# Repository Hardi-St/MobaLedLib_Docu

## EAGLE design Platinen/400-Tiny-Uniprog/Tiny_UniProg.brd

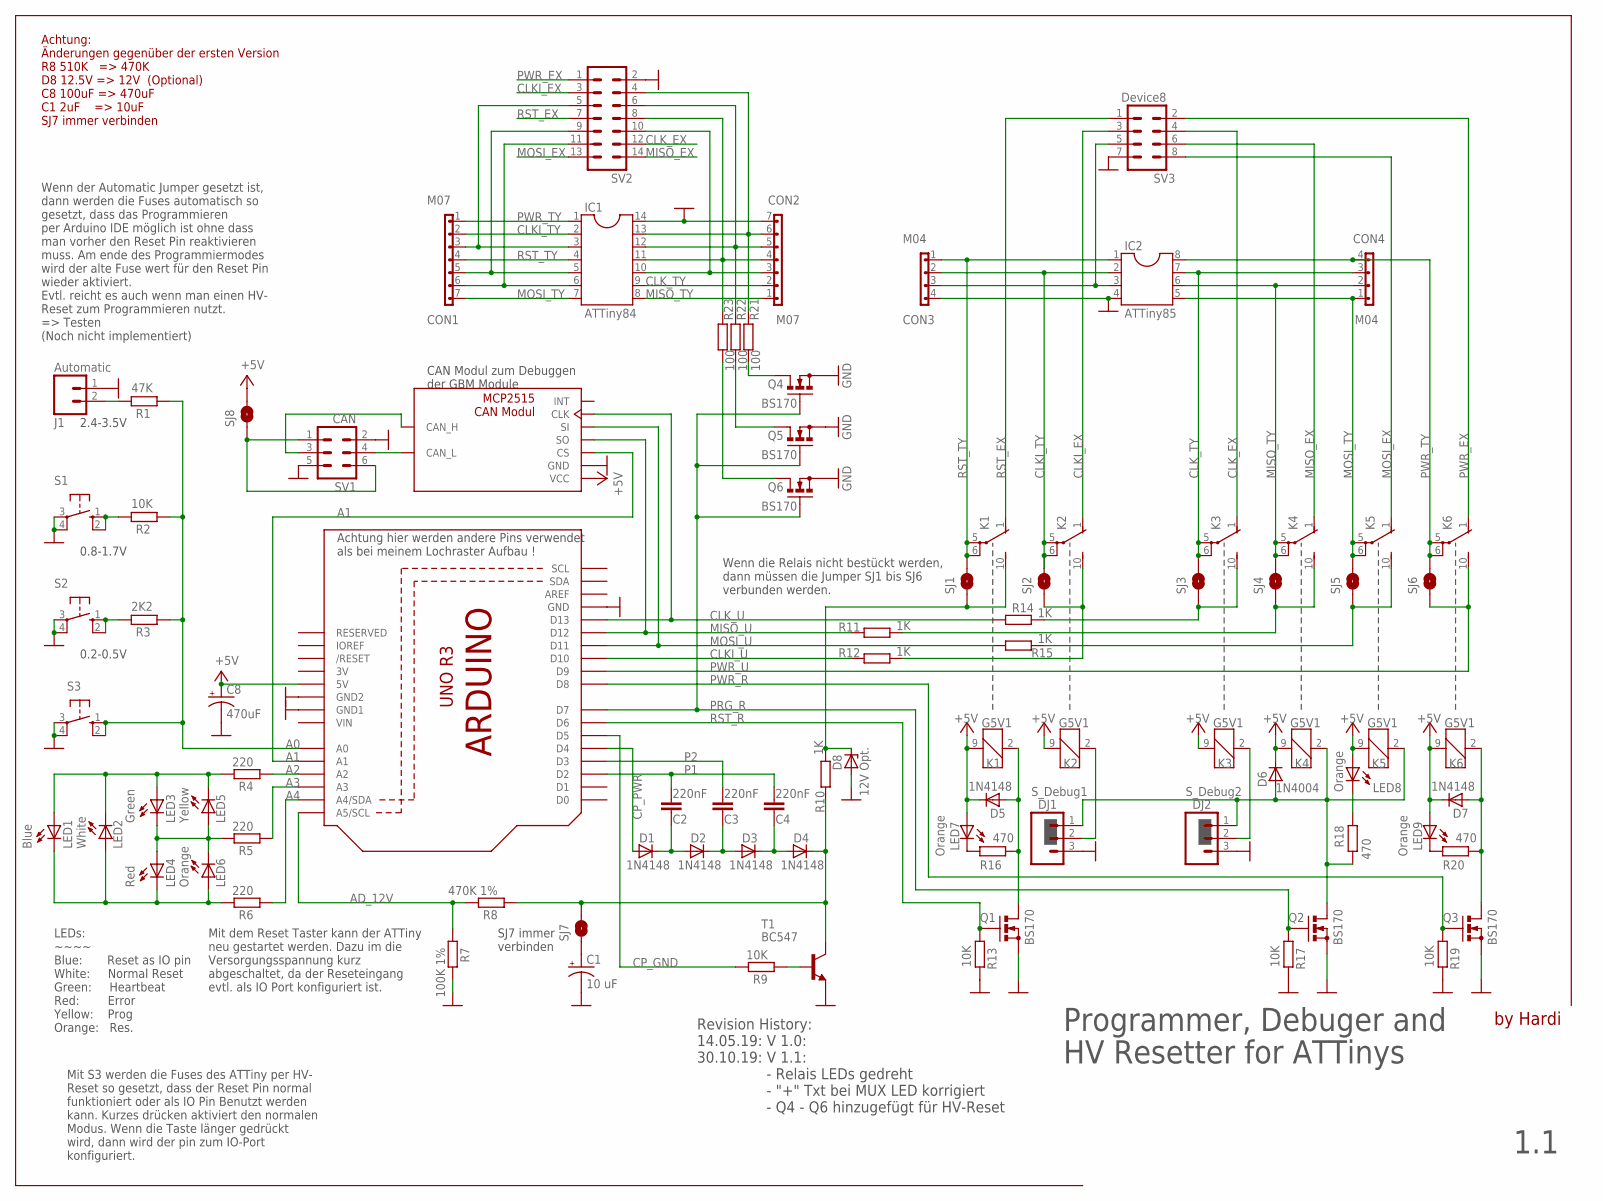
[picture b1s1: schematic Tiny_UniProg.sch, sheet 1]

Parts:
C1: 10 uF; CPOL-RADIAL-10UF-63V
C2, C3, C4: 220nF; C050-024X044
C8: 470uF; SPARKFUN-CAPACITORS_CPOL-RADIAL-100UF-25V
CAN1: MCP2515_CAN_MODUL
CON1, CON2: M07; 1X07
CON3, CON4: M04; 1X04
D1, D2, D3, D4, D5, D7: 1N4148; DO35-2
D6: 1N4004; DO35-2
D8: 12V Opt.; ZDIO-2.5
DJ1: S_Debug1; 1X03
DJ2: S_Debug2; 1X03
IC1: ATTiny84; DIL14
IC2: ATTiny85; DIL08
J1: Automatic; 1X02
K1, K2, K3, K4, K5, K6: G5V1
LED1: Blue; LED3MM
LED2: White; LED3MM
LED3: Green; LED3MM
LED4: Red; LED3MM
LED5: Yellow; LED3MM
LED6, LED7, LED8, LED9: Orange; LED3MM
Q1, Q2, Q3, Q4, Q5, Q6: BS170; SOT54E
R1: 47K; 0204/7
R2: 10K; 0204/7
R3: 2K2; 0204/2V
R4, R5, R6: 220; 0204/2V
R7: 100K 1%; 0204/2V
R8: 470K 1%; 0204/7
R9, R13, R17, R19: 10K; 0204/2V
R10, R11, R12, R14, R15: 1K; 0204/2V
R16, R18, R20: 470; 0204/2V
R21, R22, R23: 100; 0204/2V
S1, S2, S3: 10-XX; B3F-10XX
SJ1, SJ2, SJ3, SJ4, SJ5, SJ6, SJ7, SJ8: SOLDERJUMPERNO; SJ_2S-NO
SV1: CAN; ML6
SV2: ML14
SV3: Device8; CON-HARTING-ML_ML08
T1: BC547; TO92
U1: ARDUINOR3-DIMENSION; ARDUINOR3

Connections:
3V: U1.3V
+5V: C8.1 (+), CAN1.1 (VCC), D5.C, D6.C, D7.C, K1.9 (2), K2.9 (2), K3.9 (2), K4.9 (2), K5.9 (2), K6.9 (2), LED7.A, LED8.A, LED9.A, SJ8.2, U1.5V
A0: R1.1, R2.1, R3.1, S3.1 (S), S3.2 (S1), U1.A0
A1: CAN1.3 (CS), U1.A1
A2: R4.1, U1.A2
A3: R5.1, U1.A3
A4: R6.1, U1.A4 (A4/SDA)
AD_12V: R7.1, R8.2, U1.A5 (A5/SCL)
CLKI_EX: K2.1 (O), SV2.3, SV3.3
CLKI_TY: CON1.2, CON3.2, IC1.2, IC2.2, K2.5, K2.6, SJ2.2
CLKI_U: R12.1, U1.D10
CLK_EX: K3.1 (O), SV2.12, SV3.4
CLK_TY: CON2.2, CON4.3, IC1.9, IC2.7, K3.5, K3.6, SJ3.2
CLK_U: CAN1.6 (CLK), R14.1, U1.D13
CP_GND: R9.2, U1.D5
CP_PWR: D1.A, U1.D4
GND: C1.2 (-), C8.2 (-), CAN1.2 (GND), CON2.7, CON3.4, D8.A, DJ1.3, DJ2.3, IC1.14, IC2.4, J1.1, Q1.S, Q2.S, Q3.S, Q4.S, Q5.S, Q6.S, R7.2, R13.2, R17.2, R19.2, S1.3, S1.4 (P1), S2.3, S2.4 (P1), S3.3, S3.4 (P1), SV1.2, SV1.5, SV2.2, SV3.7, T1.1 (E), U1.GND, U1.GND1, U1.GND2
MISO_EX: K4.1 (O), SV2.14, SV3.6
MISO_TY: CON2.1, CON4.2, IC1.8, IC2.6, K4.5, K4.6, SJ4.2
MISO_U: CAN1.4 (SO), R11.1, U1.D12
MOSI_EX: K5.1 (O), SV2.13, SV3.8
MOSI_TY: CON1.7, CON4.1, IC1.7, IC2.5, K5.5, K5.6, SJ5.2
MOSI_U: CAN1.5 (SI), R15.1, U1.D11
unnamed: C2.2, D1.C, D2.A
unnamed: C3.2, D2.C, D3.A
unnamed: C4.2, D3.C, D4.A
unnamed: CON2.3, IC1.10, SV2.10
unnamed: R9.1, T1.2 (B)
unnamed: CAN1.8 (CAN_L), SV1.4
unnamed: D4.C, R8.1, R10.2, SJ7.2, T1.3 (C)
unnamed: CAN1.9 (CAN_H), SV1.3
unnamed: CON2.4, IC1.11, R23.2, SV2.8
unnamed: CON2.5, IC1.12, R22.2, SV2.6
unnamed: K5.10 (S), R15.2, SJ5.1
unnamed: CON2.6, IC1.13, R21.2, SV2.4
unnamed: K4.10 (S), R11.2, SJ4.1
unnamed: K3.10 (S), R14.2, SJ3.1
unnamed: DJ1.2, K2.2 (1)
unnamed: D5.A, K1.2 (1), Q1.D, R16.2
unnamed: DJ2.2, K3.2 (1)
unnamed: D8.C, K1.10 (S), R10.1, SJ1.1
unnamed: CON1.6, IC1.6, SV2.11
unnamed: K2.10 (S), R12.2, SJ2.1
unnamed: D7.A, K6.2 (1), Q3.D, R20.2
unnamed: D6.A, DJ1.1, DJ2.1, K4.2 (1), K5.2 (1), Q2.D, R18.2
unnamed: CON1.5, IC1.5, SV2.9
unnamed: J1.2, R1.2
unnamed: CON1.3, IC1.3, SV2.5
unnamed: R3.2, S2.1 (S), S2.2 (S1)
unnamed: LED1.A, LED2.K (C), LED3.A, LED5.K (C), R4.2
unnamed: LED7.K (C), R16.1
unnamed: LED8.K (C), R18.1
unnamed: LED9.K (C), R20.1
unnamed: C1.1 (+), SJ7.1
unnamed: LED3.K (C), LED4.A, LED5.A, LED6.K (C), R5.2
unnamed: LED1.K (C), LED2.A, LED4.K (C), LED6.A, R6.2
unnamed: SJ8.1, SV1.1, SV1.6
unnamed: CON3.3, IC2.3, SV3.5
unnamed: R2.2, S1.1 (S), S1.2 (S1)
unnamed: Q4.D, R21.1
unnamed: Q5.D, R22.1
unnamed: Q6.D, R23.1
P1: C2.1, C4.1, U1.D2
P2: C3.1, U1.D3
PRG_R: Q2.G, Q4.G, Q5.G, Q6.G, R17.1, U1.D7
PWR_EX: K6.1 (O), SV2.1, SV3.2
PWR_R: Q3.G, R19.1, U1.D8
PWR_TY: CON1.1, CON4.4, IC1.1, IC2.8, K6.5, K6.6, SJ6.2
PWR_U: K6.10 (S), SJ6.1, U1.D9
RST_EX: K1.1 (O), SV2.7, SV3.1
RST_R: Q1.G, R13.1, U1.D6
RST_TY: CON1.4, CON3.1, IC1.4, IC2.1, K1.5, K1.6, SJ1.2
VIN: U1.VIN

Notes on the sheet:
Mit S3 werden die Fuses des ATTiny per HV- Reset so gesetzt, dass der Reset Pin normal funktioniert oder als IO Pin Benutzt werden kann. Kurzes drücken aktiviert den normalen Modus. Wenn die Taste länger gedrückt wird, dann wird der pin zum IO-Port konfiguriert.
Mit dem Reset Taster kann der ATTiny neu gestartet werden. Dazu im die Versorgungsspannung kurz abgeschaltet, da der Reseteingang evtl. als IO Port konfiguriert ist.
Wenn der Automatic Jumper gesetzt ist, dann werden die Fuses automatisch so gesetzt, dass das Programmieren per Arduino IDE möglich ist ohne dass man vorher den Reset Pin reaktivieren muss. Am ende des Programmiermodes wird der alte Fuse wert für den Reset Pin wieder aktiviert. Evtl. reicht es auch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
CAN Modul zum Debuggen der GBM Module
LEDs: ~~~~ Blue: Reset as IO pin White: Normal Reset Green: Heartbeat Red: Error Yellow: Prog Orange: Res.
by Hardi
Programmer, Debuger and HV Resetter for ATTinys
Wenn die Relais nicht bestückt werden, dann müssen die Jumper SJ1 bis SJ6 verbunden werden.
0.2-0.5V
0.8-1.7V
2.4-3.5V
Achtung: Änderungen gegenüber der ersten Version R8 510K => 470K D8 12.5V => 12V (Optional) C8 100uF => 470uF C1 2uF => 10uF SJ7 immer verbinden
SJ7 immer verbinden
Achtung hier werden andere Pins verwendet als bei meinem Lochraster Aufbau !
Revision History: 14.05.19: V 1.0: 30.10.19: V 1.1: - Relais LEDs gedreht - "+" Txt bei MUX LED korrigiert - Q4 - Q6 hinzugefügt für HV-Reset
1.1

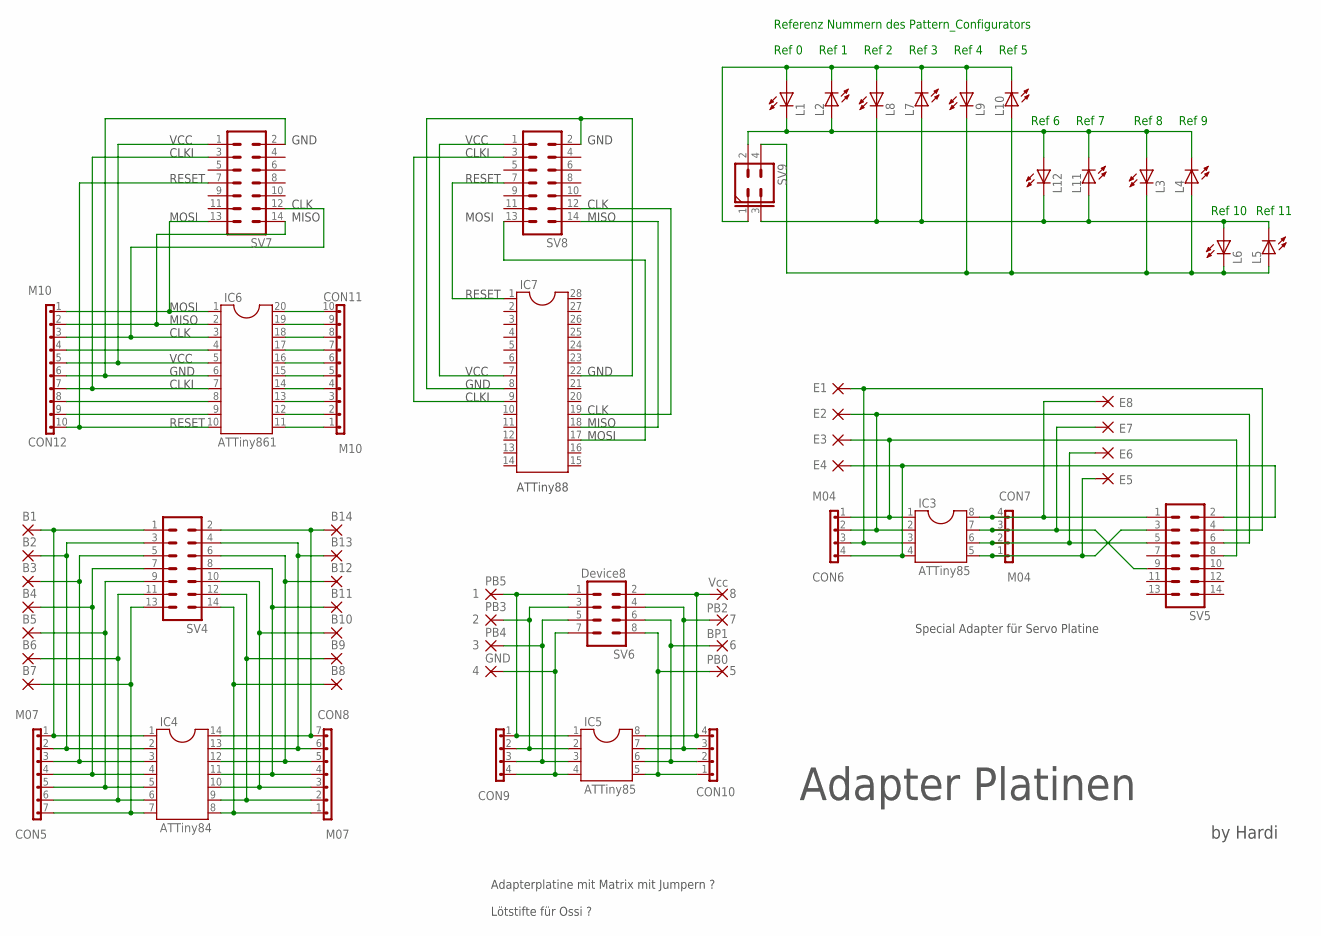
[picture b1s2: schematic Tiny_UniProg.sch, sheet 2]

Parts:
1: PB5; 2,54/1,0
2: PB3; 2,54/1,0
3: PB4; 2,54/1,0
4: GND; 2,54/1,0
5: PB0; 2,54/1,0
6: BP1; 2,54/1,0
7: PB2; 2,54/1,0
8: Vcc; 2,54/1,0
B1, B2, B3, B4, B5, B6, B7, B8, B9, B10, B11, B12, B13, B14: 2,54/1,0
CON5, CON8: M07; 1X07
CON6, CON7, CON9, CON10: M04; 1X04
CON11, CON12: M10; 1X10
E1, E2, E3, E4, E5, E6, E7, E8: 2,54/1,0
IC3, IC5: ATTiny85; DIL08
IC4: ATTiny84; DIL14
IC6: ATTiny861; DIL20
IC7: DIL28-3
L1, L2, L3, L4, L5, L6, L7, L8, L9, L10, L11, L12: LED3MM
SV4, SV5, SV7, SV8: ML14
SV6: Device8; CON-HARTING-ML_ML08
SV9: MA02-2MUX-SIGNAL; MUX-SIGNAL

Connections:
unnamed: 4.1, CON9.4, IC5.4, SV6.7
unnamed: 3.1, CON9.3, IC5.3, SV6.5
unnamed: 2.1, CON9.2, IC5.2, SV6.3
unnamed: 1.1, CON9.1, IC5.1, SV6.1
unnamed: 5.1, CON10.1, IC5.5, SV6.8
unnamed: 6.1, CON10.2, IC5.6, SV6.6
unnamed: 7.1, CON10.3, IC5.7, SV6.4
unnamed: B8.1, CON8.1, IC4.8, SV4.14
unnamed: B9.1, CON8.2, IC4.9, SV4.12
unnamed: B10.1, CON8.3, IC4.10, SV4.10
unnamed: B11.1, CON8.4, IC4.11, SV4.8
unnamed: B12.1, CON8.5, IC4.12, SV4.6
unnamed: B13.1, CON8.6, IC4.13, SV4.4
unnamed: B14.1, CON8.7, IC4.14, SV4.2
unnamed: B7.1, CON5.7, IC4.7, SV4.13
unnamed: B6.1, CON5.6, IC4.6, SV4.11
unnamed: B5.1, CON5.5, IC4.5, SV4.9
unnamed: B4.1, CON5.4, IC4.4, SV4.7
unnamed: B3.1, CON5.3, IC4.3, SV4.5
unnamed: B2.1, CON5.2, IC4.2, SV4.3
unnamed: B1.1, CON5.1, IC4.1, SV4.1
unnamed: 8.1, CON10.4, IC5.8, SV6.2
unnamed: CON7.4, E8.1, IC3.8, SV5.1
unnamed: CON6.4, E4.1, IC3.4, SV5.2
unnamed: CON7.3, E7.1, IC3.7, SV5.9
unnamed: CON7.2, E6.1, IC3.6, SV5.5
unnamed: CON7.1, E5.1, IC3.5, SV5.3
unnamed: CON6.1, E3.1, IC3.1, SV5.8
unnamed: CON6.2, E2.1, IC3.2, SV5.6
unnamed: CON6.3, E1.1, IC3.3, SV5.4
unnamed: CON12.10, IC6.10, SV7.7
unnamed: CON12.7, IC6.7, SV7.3
unnamed: CON12.6, IC6.6, SV7.2
unnamed: CON12.5, IC6.5, SV7.1
unnamed: CON12.3, IC6.3, SV7.12
unnamed: CON12.2, IC6.2, SV7.14
unnamed: CON12.1, IC6.1, SV7.13
unnamed: CON12.4, IC6.4
unnamed: CON12.8, IC6.8
unnamed: CON12.9, IC6.9
unnamed: CON11.1, IC6.11
unnamed: CON11.2, IC6.12
unnamed: CON11.3, IC6.13
unnamed: CON11.4, IC6.14
unnamed: CON11.5, IC6.15
unnamed: CON11.6, IC6.16
unnamed: CON11.7, IC6.17
unnamed: CON11.8, IC6.18
unnamed: CON11.9, IC6.19
unnamed: CON11.10, IC6.20
unnamed: IC7.9, SV8.3
unnamed: IC7.8, IC7.22, SV8.2
unnamed: IC7.7, SV8.1
unnamed: IC7.1, SV8.7
unnamed: IC7.17, SV8.13
unnamed: IC7.18, SV8.14
unnamed: L1.K (C), L2.A, L3.A, L4.K (C), L11.K (C), L12.A, SV9.2
unnamed: IC7.19, SV8.12
unnamed: L1.A, L2.K (C), L7.K (C), L8.A, L9.A, L10.K (C), SV9.1
unnamed: L3.K (C), L4.A, L5.A, L6.K (C), L9.K (C), L10.A, SV9.4
unnamed: L5.K (C), L6.A, L7.A, L8.K (C), L11.A, L12.K (C), SV9.3

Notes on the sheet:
Adapter Platinen
Special Adapter für Servo Platine
Adapterplatine mit Matrix mit Jumpern ? Lötstifte für Ossi ?
by Hardi
MOSI
MISO
CLK
VCC
GND
RESET
CLKI
ATTiny88
Ref 0
Ref 1
Ref 2
Ref 3
Ref 4
Ref 5
Ref 6
Ref 7
Ref 8
Ref 9
Ref 10
Ref 11
Referenz Nummern des Pattern_Configurators

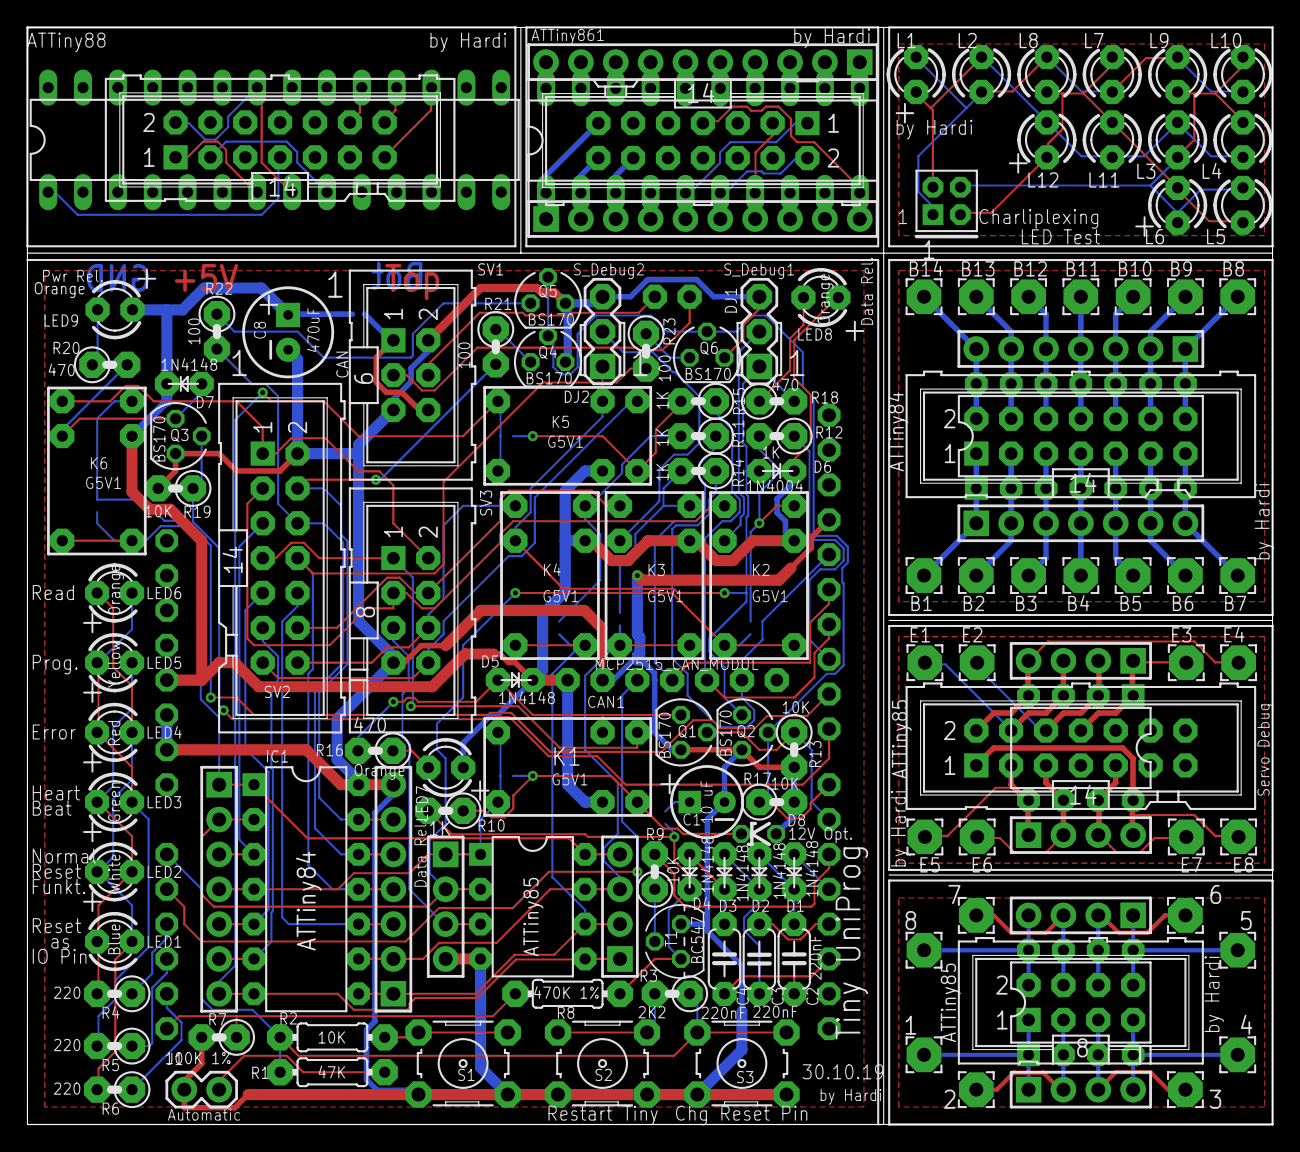
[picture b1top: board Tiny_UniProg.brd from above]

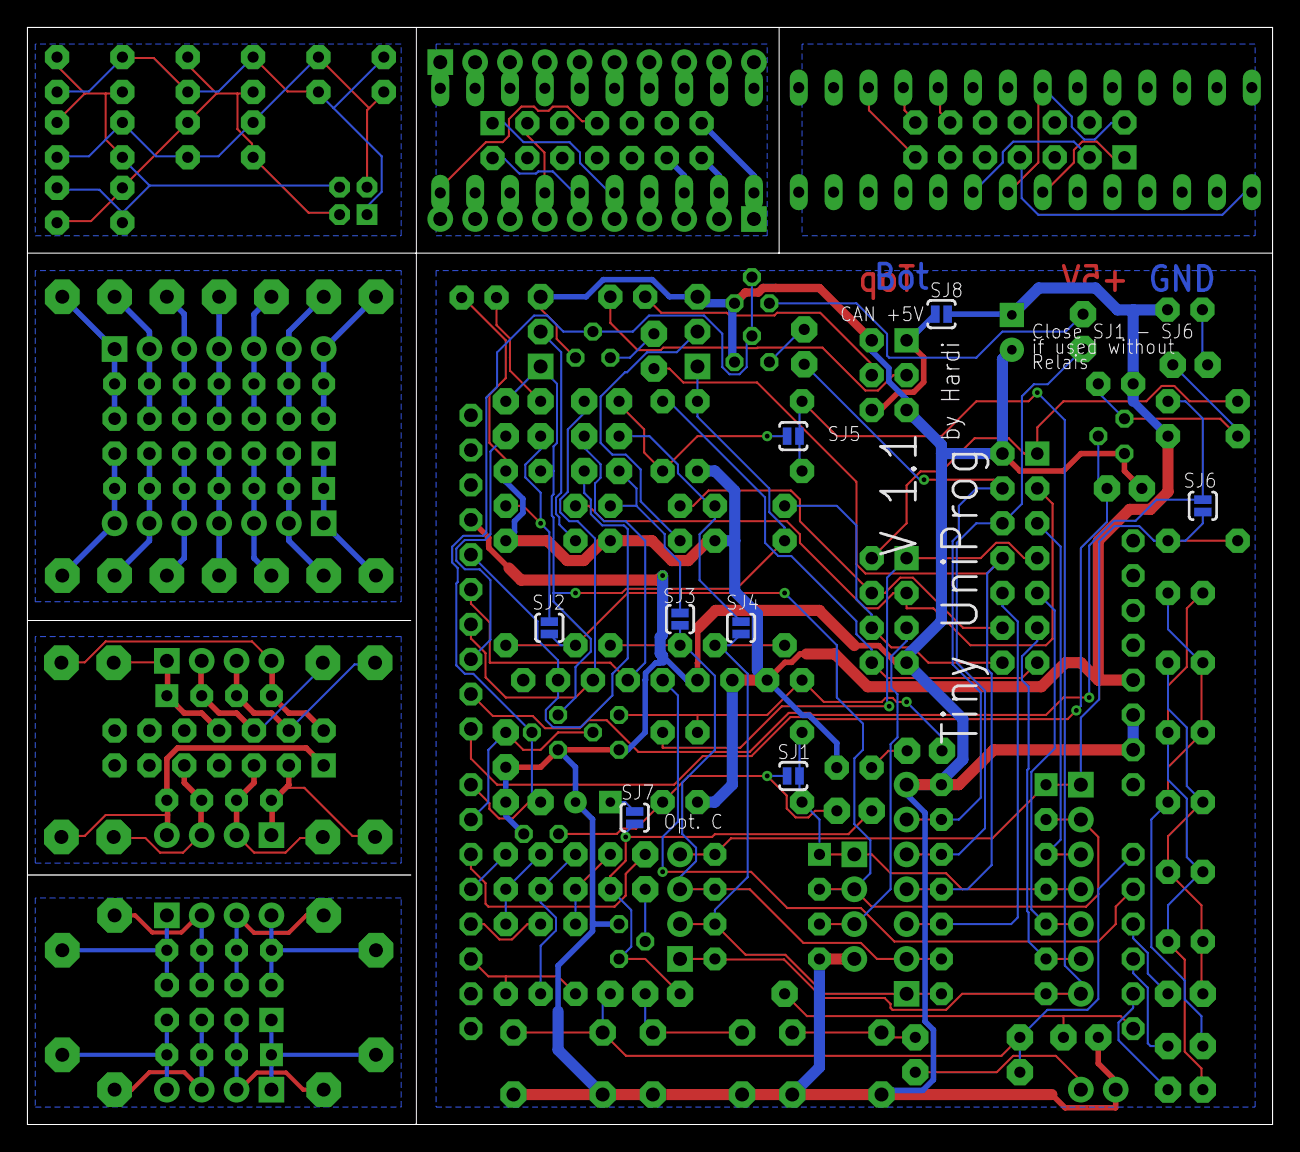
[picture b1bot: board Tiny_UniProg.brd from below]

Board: 2 copper layers, 90.7 x 80.0 mm, 144 parts (8 on the bottom side), 132 nets.

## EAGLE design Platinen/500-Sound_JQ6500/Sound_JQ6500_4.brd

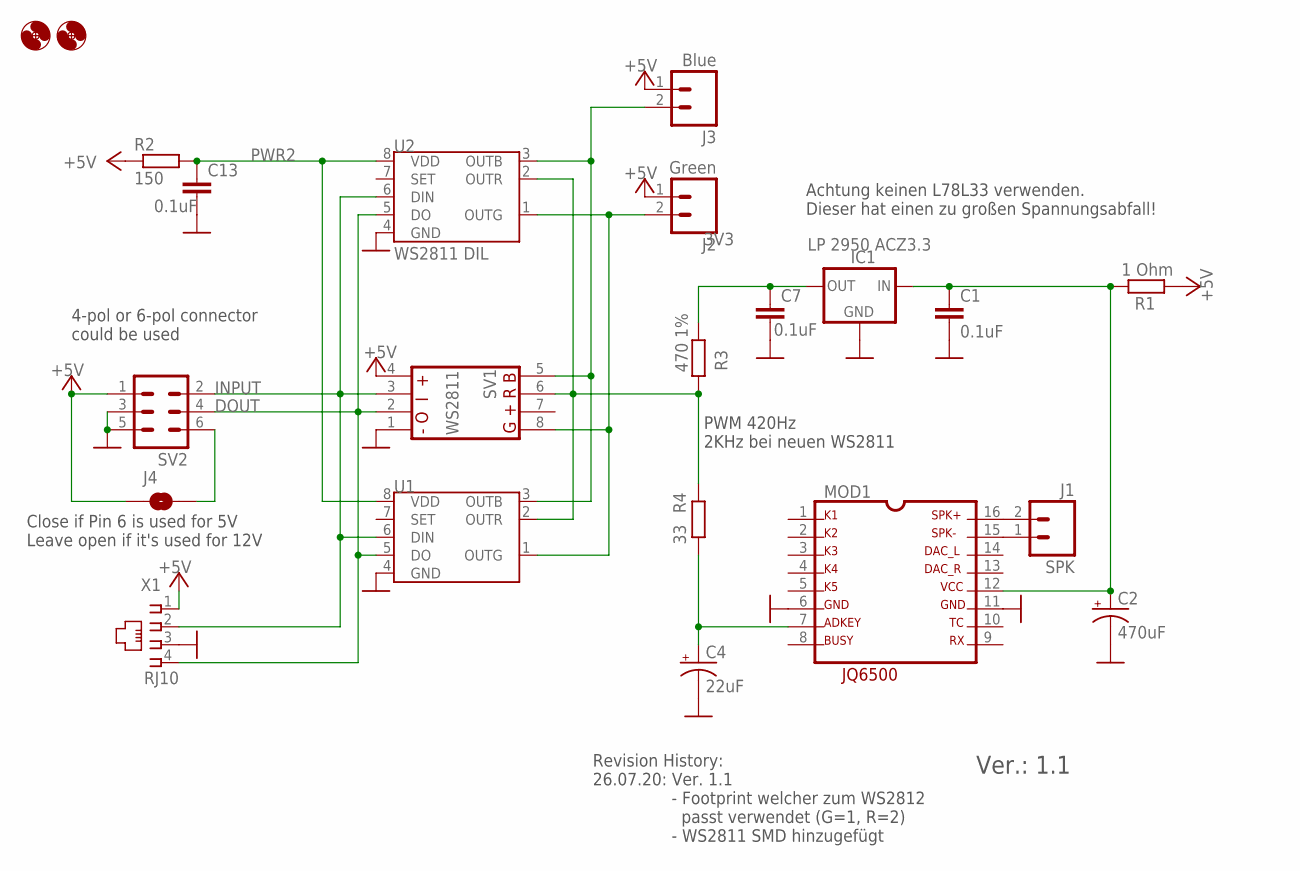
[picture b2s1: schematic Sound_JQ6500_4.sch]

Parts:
C1, C7, C13: 0.1uF; CAP-PTH-SMALL-KIT
C2: 470uF; SPARKFUN-CAPACITORS_CPOL-RADIAL-100UF-25V
C4: 22uF; CAPACITOR_CPOL-RADIAL-22UF
H1, H3: MOUNT-HOLE3.0; 3,0
IC1: LP 2950 ACZ3.3; 78LXX
J1: SPK; 1X02
J2: Green; 1X02
J3: Blue; 1X02
J4: SOLDERJUMPERNO; SJ_2S-NO
MOD1: JQ6500
R1: 1 Ohm; RCL_0204/5
R2: 150; RCL_0204/5
R3: 470 1%; RCL_0204/5
R4: 33; RCL_0204/5
SV1: S3PO_MODUL_WS2811_SOUND_MP3-TF-16P_WS2811_AND_ATT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; S3PO_MODUL_WS2811_SOUND_MP3-TF-16P_WS2811_AND_ATTINY_PUSHBU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
SV2: ML6
U1: WS2811 DIL; SOP8
U2: WS2811 DIL; S3PO_MODUL_WS2811_SOUND_MP3-TF-16P_WS2811_AND_ATTINY_WS2811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
X1: RJ10

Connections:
3V3: C7.1, IC1.OUT, R3.1
+5V: J2.1, J3.1, J4.1, R1.1, R2.1, SV1.4 (GND), SV2.1, X1.1
B2: J3.2, SV1.5 (OUTG), U1.3 (OUTB), U2.3 (OUTB)
DOUT: SV1.2 (DIN), SV2.4, U1.5 (DO), U2.5 (DO), X1.4
G2: J2.2, SV1.8 (OUTB), U1.1 (OUTG), U2.1 (OUTG)
GND: C1.2, C2.2 (-), C4.2 (-), C7.2, C13.2, IC1.GND, MOD1.6, MOD1.11, SV1.1 (VDD), SV2.3, SV2.5, U1.4 (GND), U2.4 (GND), X1.3
INPUT: SV1.3 (DO), SV2.2, U1.6 (DIN), U2.6 (DIN), X1.2
unnamed: J1.1, MOD1.15
unnamed: J1.2, MOD1.16
unnamed: C1.1, C2.1 (+), IC1.IN, MOD1.12, R1.2
unnamed: J4.2, SV2.6
unnamed: C4.1 (+), MOD1.7, R4.2
PWR2: C13.1, R2.2, U1.8 (VDD), U2.8 (VDD)
R1: R3.2, R4.1, SV1.6 (OUT+), U1.2 (OUTR), U2.2 (OUTR)

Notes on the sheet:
PWM 420Hz 2KHz bei neuen WS2811
Close if Pin 6 is used for 5V Leave open if it's used for 12V
4-pol or 6-pol connector could be used
Achtung keinen L78L33 verwenden. Dieser hat einen zu großen Spannungsabfall!
Ver.: 1.1
Revision History: 26.07.20: Ver. 1.1 - Footprint welcher zum WS2812 passt verwendet (G=1, R=2) - WS2811 SMD hinzugefügt

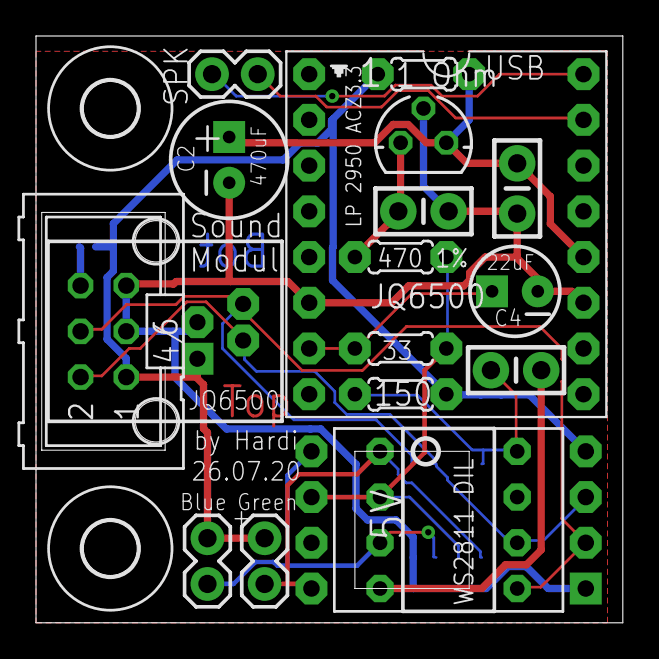
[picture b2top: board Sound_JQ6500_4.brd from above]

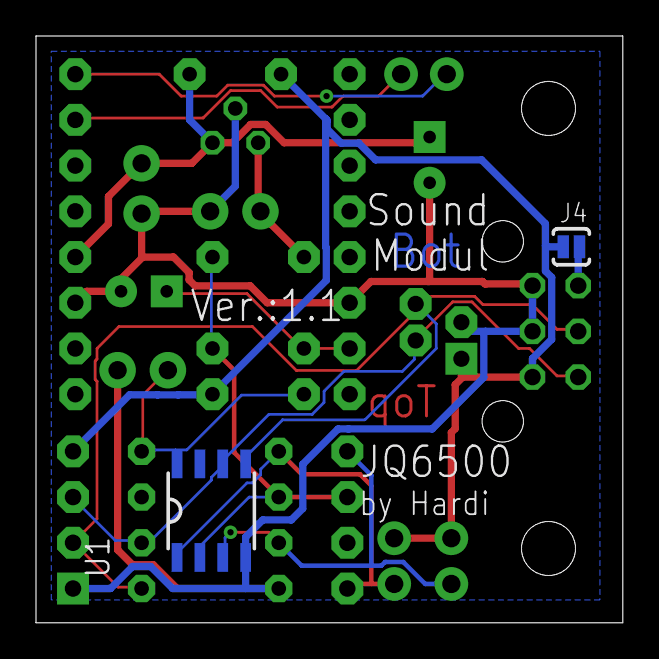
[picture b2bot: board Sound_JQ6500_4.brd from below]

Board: 2 copper layers, 32.6 x 32.6 mm, 22 parts (2 on the bottom side), 14 nets.

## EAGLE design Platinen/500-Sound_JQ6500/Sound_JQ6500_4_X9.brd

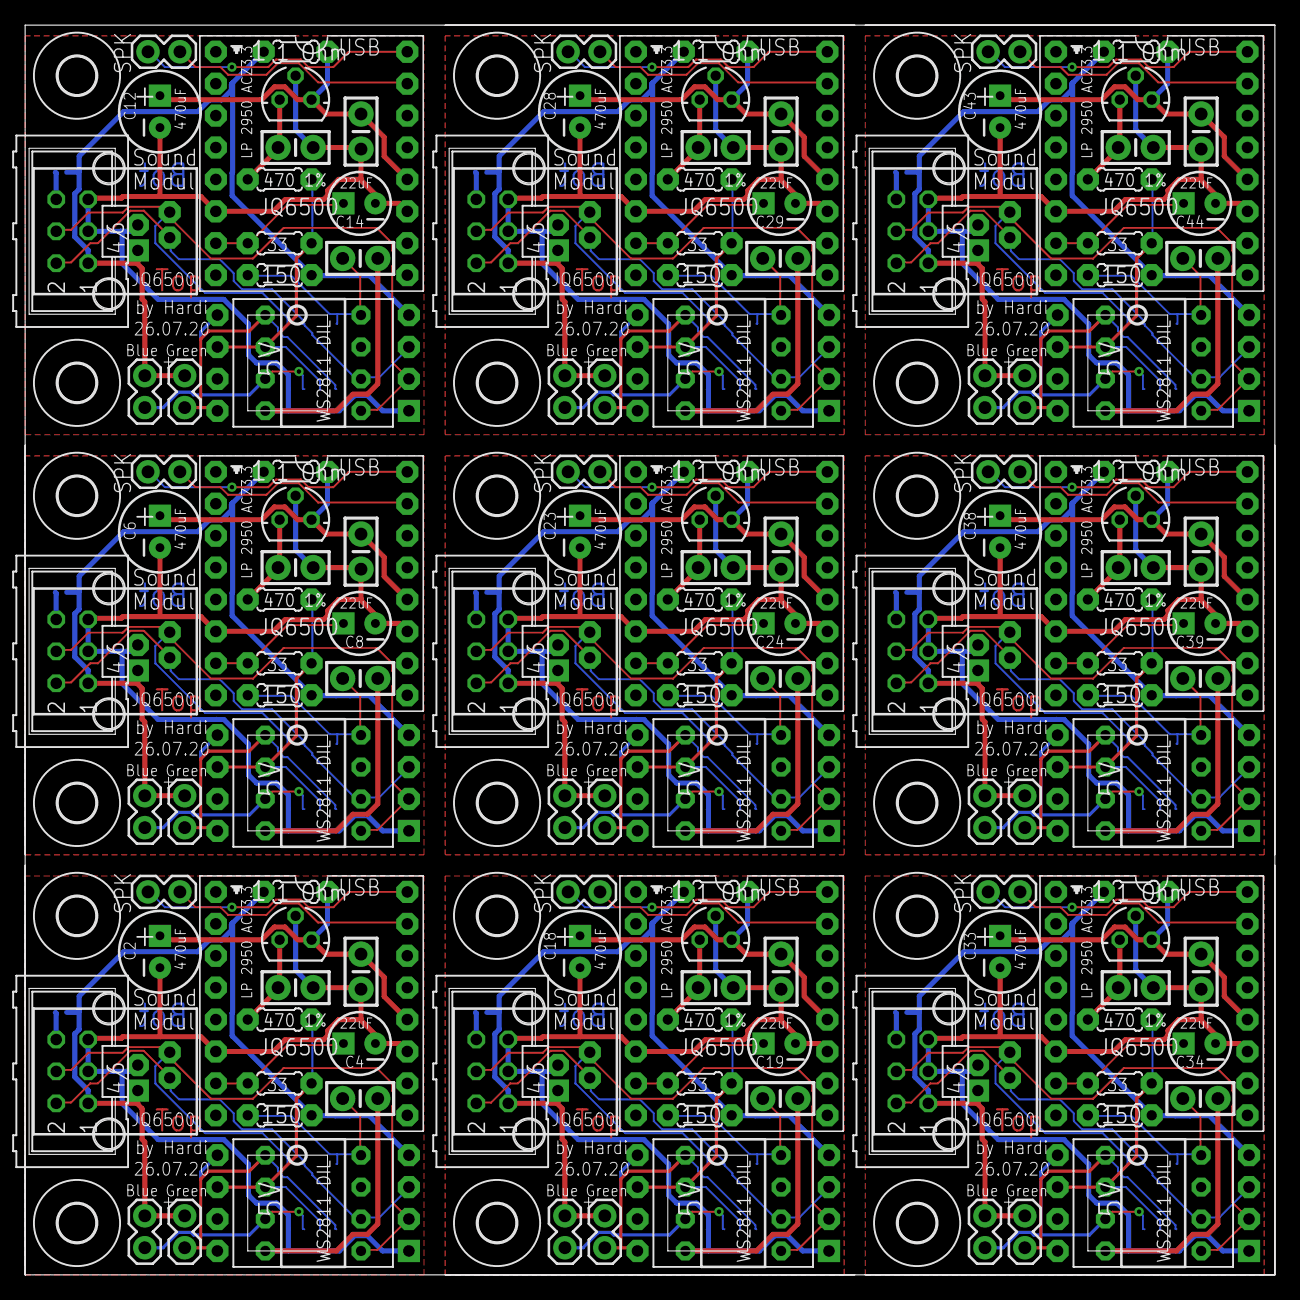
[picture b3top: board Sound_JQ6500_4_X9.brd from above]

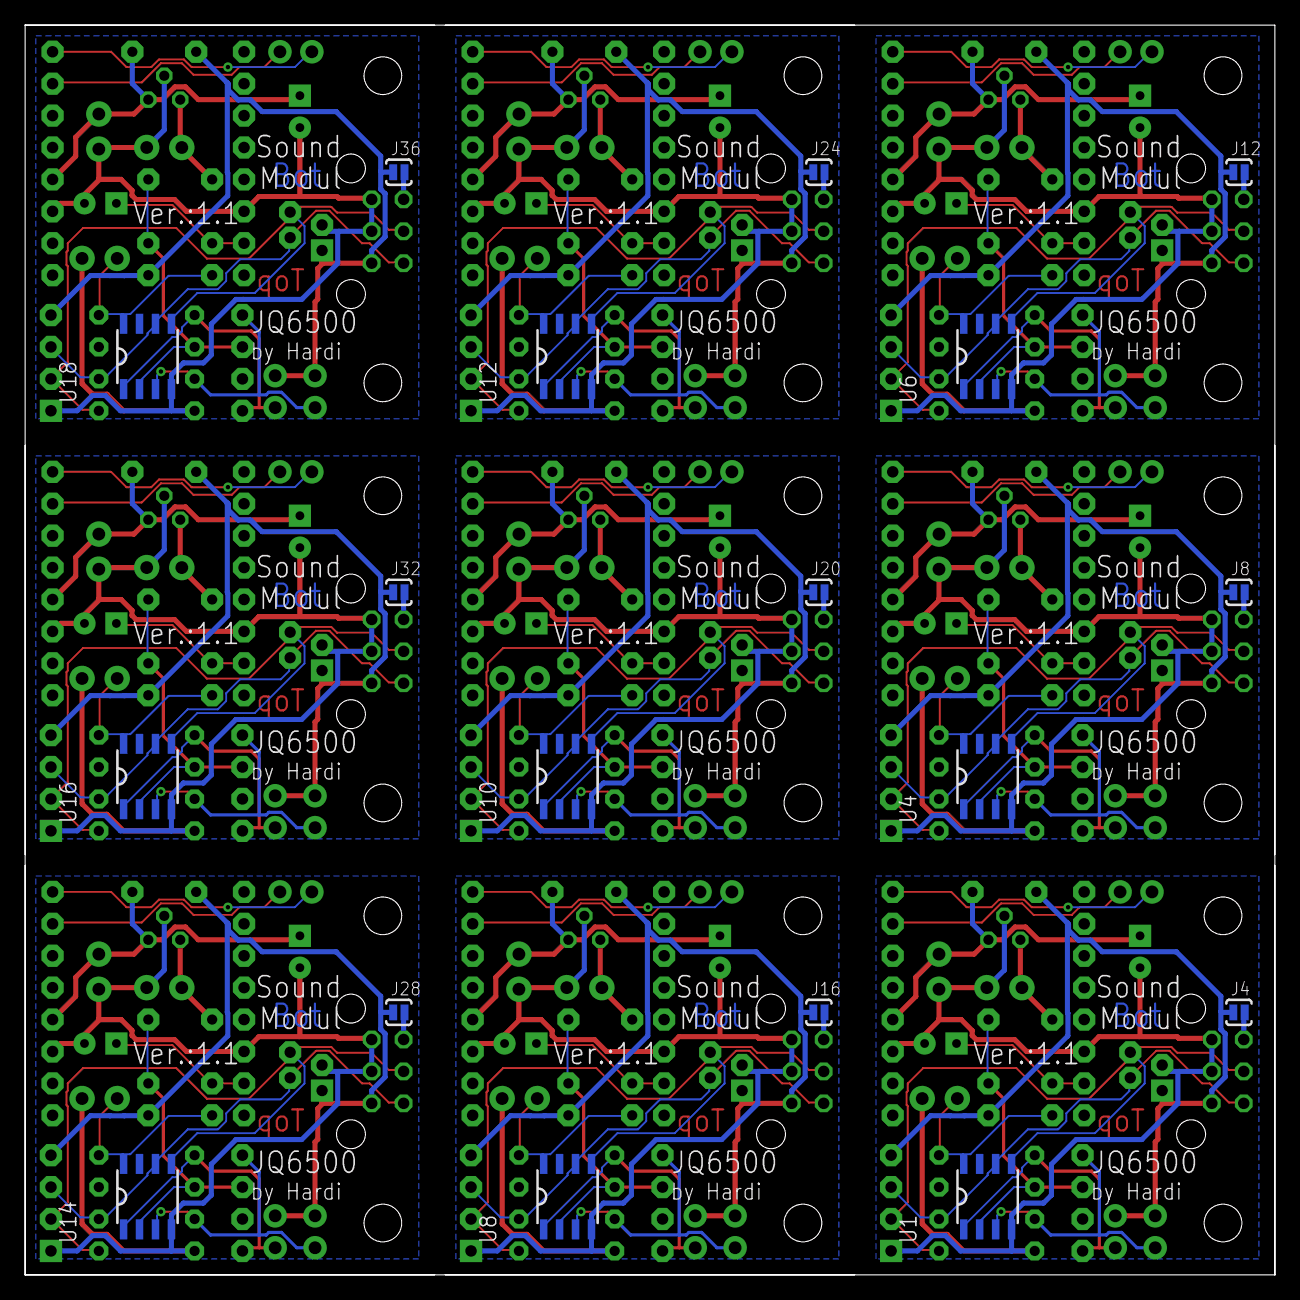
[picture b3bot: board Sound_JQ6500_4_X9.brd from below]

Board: 2 copper layers, 99.5 x 99.5 mm, 198 parts (18 on the bottom side), 126 nets.

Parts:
C1, C3, C5, C7, C9, C10, C11, C13, C15, C16, C17, C20, C21, C22, C25, C26, C27, C30, C31, C32, C35, C36, C37, C40, C41, C42, C45: 0.1uF; CAP-PTH-SMALL-KIT
C2, C6, C12, C18, C23, C28, C33, C38, C43: 470uF; SPARKFUN-CAPACITORS_CPOL-RADIAL-100UF-25V
C4, C8, C14, C19, C24, C29, C34, C39, C44: 22uF; CAPACITOR_CPOL-RADIAL-22UF
H1, H2, H3, H4, H5, H6, H7, H8, H9, H10, H11, H12, H13, H14, H15, H16, H17, H18: MOUNT-HOLE3.0; 3,0
IC1, IC2, IC3, IC4, IC5, IC6, IC7, IC8, IC9: LP 2950 ACZ3.3; 78LXX
J1, J5, J9, J13, J17, J21, J25, J29, J33: SPK; 1X02
J2, J6, J10, J14, J18, J22, J26, J30, J34: Green; 1X02
J3, J7, J11, J15, J19, J23, J27, J31, J35: Blue; 1X02
J4, J8, J12, J16, J20, J24, J28, J32, J36: SOLDERJUMPERNO; SJ_2S-NO
MOD1, MOD2, MOD3, MOD4, MOD5, MOD6, MOD7, MOD8, MOD9: JQ6500
R1, R5, R9, R13, R17, R21, R25, R29, R33: 1 Ohm; RCL_0204/5
R2, R6, R10, R14, R18, R22, R26, R30, R34: 150; RCL_0204/5
R3, R7, R11, R15, R19, R23, R27, R31, R35: 470 1%; RCL_0204/5
R4, R8, R12, R16, R20, R24, R28, R32, R36: 33; RCL_0204/5
SV1, SV3, SV5, SV7, SV9, SV11, SV13, SV15, SV17: S3PO_MODUL_WS2811_SOUND_MP3-TF-16P_WS2811_AND_ATTINY_PUSHBU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
SV2, SV4, SV6, SV8, SV10, SV12, SV14, SV16, SV18: ML6
U1, U4, U6, U8, U10, U12, U14, U16, U18: WS2811 DIL; SOP8
U2, U3, U5, U7, U9, U11, U13, U15, U17: WS2811 DIL; S3PO_MODUL_WS2811_SOUND_MP3-TF-16P_WS2811_AND_ATTINY_WS2811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
X1, X2, X3, X4, X5, X6, X7, X8, X9: RJ10

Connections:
3V1: C9.1, IC2.OUT, R7.1
3V2: C15.1, IC3.OUT, R11.1
3V3: C7.1, IC1.OUT, R3.1
3V4: C20.1, IC4.OUT, R15.1
3V5: C25.1, IC5.OUT, R19.1
3V6: C30.1, IC6.OUT, R23.1
3V7: C35.1, IC7.OUT, R27.1
3V8: C40.1, IC8.OUT, R31.1
3V9: C45.1, IC9.OUT, R35.1
+5V: J2.1, J3.1, J4.1, R1.1, R2.1, SV1.4, SV2.1, X1.1
+5V1: J6.1, J7.1, J8.1, R5.1, R6.1, SV3.4, SV4.1, X2.1
+5V2: J10.1, J11.1, J12.1, R9.1, R10.1, SV5.4, SV6.1, X3.1
+5V3: J14.1, J15.1, J16.1, R13.1, R14.1, SV7.4, SV8.1, X4.1
+5V4: J18.1, J19.1, J20.1, R17.1, R18.1, SV9.4, SV10.1, X5.1
+5V5: J22.1, J23.1, J24.1, R21.1, R22.1, SV11.4, SV12.1, X6.1
+5V6: J26.1, J27.1, J28.1, R25.1, R26.1, SV13.4, SV14.1, X7.1
+5V7: J30.1, J31.1, J32.1, R29.1, R30.1, SV15.4, SV16.1, X8.1
+5V8: J34.1, J35.1, J36.1, R33.1, R34.1, SV17.4, SV18.1, X9.1
B1: J7.2, SV3.5, U3.3, U4.3
B2: J3.2, SV1.5, U1.3, U2.3
B3: J11.2, SV5.5, U5.3, U6.3
B4: J15.2, SV7.5, U7.3, U8.3
B5: J19.2, SV9.5, U9.3, U10.3
B6: J23.2, SV11.5, U11.3, U12.3
B7: J27.2, SV13.5, U13.3, U14.3
B8: J31.2, SV15.5, U15.3, U16.3
B9: J35.2, SV17.5, U17.3, U18.3
DOUT: SV1.2, SV2.4, U1.5, U2.5, X1.4
DOUT1: SV3.2, SV4.4, U3.5, U4.5, X2.4
DOUT2: SV5.2, SV6.4, U5.5, U6.5, X3.4
DOUT3: SV7.2, SV8.4, U7.5, U8.5, X4.4
DOUT4: SV9.2, SV10.4, U9.5, U10.5, X5.4
DOUT5: SV11.2, SV12.4, U11.5, U12.5, X6.4
DOUT6: SV13.2, SV14.4, U13.5, U14.5, X7.4
DOUT7: SV15.2, SV16.4, U15.5, U16.5, X8.4
DOUT8: SV17.2, SV18.4, U17.5, U18.5, X9.4
G1: J6.2, SV3.8, U3.1, U4.1
G2: J2.2, SV1.8, U1.1, U2.1
G3: J10.2, SV5.8, U5.1, U6.1
G4: J14.2, SV7.8, U7.1, U8.1
G5: J18.2, SV9.8, U9.1, U10.1
G6: J22.2, SV11.8, U11.1, U12.1
G7: J26.2, SV13.8, U13.1, U14.1
G8: J30.2, SV15.8, U15.1, U16.1
G9: J34.2, SV17.8, U17.1, U18.1
GND: C1.2, C2.2, C4.2, C7.2, C13.2, IC1.GND, MOD1.6, MOD1.11, SV1.1, SV2.3, SV2.5, U1.4, U2.4, X1.3
GND1: C3.2, C5.2, C6.2, C8.2, C9.2, IC2.GND, MOD2.6, MOD2.11, SV3.1, SV4.3, SV4.5, U3.4, U4.4, X2.3
GND2: C10.2, C11.2, C12.2, C14.2, C15.2, IC3.GND, MOD3.6, MOD3.11, SV5.1, SV6.3, SV6.5, U5.4, U6.4, X3.3
GND3: C16.2, C17.2, C18.2, C19.2, C20.2, IC4.GND, MOD4.6, MOD4.11, SV7.1, SV8.3, SV8.5, U7.4, U8.4, X4.3
GND4: C21.2, C22.2, C23.2, C24.2, C25.2, IC5.GND, MOD5.6, MOD5.11, SV9.1, SV10.3, SV10.5, U9.4, U10.4, X5.3
GND5: C26.2, C27.2, C28.2, C29.2, C30.2, IC6.GND, MOD6.6, MOD6.11, SV11.1, SV12.3, SV12.5, U11.4, U12.4, X6.3
GND6: C31.2, C32.2, C33.2, C34.2, C35.2, IC7.GND, MOD7.6, MOD7.11, SV13.1, SV14.3, SV14.5, U13.4, U14.4, X7.3
GND7: C36.2, C37.2, C38.2, C39.2, C40.2, IC8.GND, MOD8.6, MOD8.11, SV15.1, SV16.3, SV16.5, U15.4, U16.4, X8.3
GND8: C41.2, C42.2, C43.2, C44.2, C45.2, IC9.GND, MOD9.6, MOD9.11, SV17.1, SV18.3, SV18.5, U17.4, U18.4, X9.3
INPUT: SV1.3, SV2.2, U1.6, U2.6, X1.2
INPUT1: SV3.3, SV4.2, U3.6, U4.6, X2.2
INPUT2: SV5.3, SV6.2, U5.6, U6.6, X3.2
INPUT3: SV7.3, SV8.2, U7.6, U8.6, X4.2
INPUT4: SV9.3, SV10.2, U9.6, U10.6, X5.2
INPUT5: SV11.3, SV12.2, U11.6, U12.6, X6.2
INPUT6: SV13.3, SV14.2, U13.6, U14.6, X7.2
INPUT7: SV15.3, SV16.2, U15.6, U16.6, X8.2
INPUT8: SV17.3, SV18.2, U17.6, U18.6, X9.2
unnamed: J1.1, MOD1.15
unnamed: J1.2, MOD1.16
unnamed: C1.1, C2.1, IC1.IN, MOD1.12, R1.2
unnamed: J4.2, SV2.6
unnamed: C8.1, MOD2.7, R8.2
unnamed: C3.1, C6.1, IC2.IN, MOD2.12, R5.2
unnamed: C4.1, MOD1.7, R4.2
unnamed: J5.1, MOD2.15
unnamed: J5.2, MOD2.16
unnamed: J8.2, SV4.6
unnamed: C14.1, MOD3.7, R12.2
unnamed: C10.1, C12.1, IC3.IN, MOD3.12, R9.2
unnamed: J9.1, MOD3.15
unnamed: J9.2, MOD3.16
unnamed: J12.2, SV6.6
unnamed: C19.1, MOD4.7, R16.2
unnamed: C16.1, C18.1, IC4.IN, MOD4.12, R13.2
unnamed: J13.1, MOD4.15
unnamed: J13.2, MOD4.16
unnamed: J16.2, SV8.6
unnamed: C24.1, MOD5.7, R20.2
unnamed: C21.1, C23.1, IC5.IN, MOD5.12, R17.2
unnamed: J17.1, MOD5.15
unnamed: J17.2, MOD5.16
unnamed: J20.2, SV10.6
unnamed: C29.1, MOD6.7, R24.2
unnamed: C26.1, C28.1, IC6.IN, MOD6.12, R21.2
unnamed: J21.1, MOD6.15
unnamed: J21.2, MOD6.16
unnamed: J24.2, SV12.6
unnamed: C34.1, MOD7.7, R28.2
unnamed: C31.1, C33.1, IC7.IN, MOD7.12, R25.2
unnamed: J25.1, MOD7.15
unnamed: J25.2, MOD7.16
unnamed: J28.2, SV14.6
unnamed: C39.1, MOD8.7, R32.2
unnamed: C36.1, C38.1, IC8.IN, MOD8.12, R29.2
unnamed: J29.1, MOD8.15
unnamed: J29.2, MOD8.16
unnamed: J32.2, SV16.6
unnamed: C44.1, MOD9.7, R36.2
unnamed: C41.1, C43.1, IC9.IN, MOD9.12, R33.2
unnamed: J33.1, MOD9.15
unnamed: J33.2, MOD9.16
unnamed: J36.2, SV18.6
PWR1: C5.1, R6.2, U3.8, U4.8
PWR2: C13.1, R2.2, U1.8, U2.8
PWR3: C11.1, R10.2, U5.8, U6.8
PWR4: C17.1, R14.2, U7.8, U8.8
PWR5: C22.1, R18.2, U9.8, U10.8
PWR6: C27.1, R22.2, U11.8, U12.8
PWR7: C32.1, R26.2, U13.8, U14.8
PWR8: C37.1, R30.2, U15.8, U16.8
PWR9: C42.1, R34.2, U17.8, U18.8
R1: R3.2, R4.1, SV1.6, U1.2, U2.2
R2: R7.2, R8.1, SV3.6, U3.2, U4.2
R3: R11.2, R12.1, SV5.6, U5.2, U6.2
R4: R15.2, R16.1, SV7.6, U7.2, U8.2
R5: R19.2, R20.1, SV9.6, U9.2, U10.2
R6: R23.2, R24.1, SV11.6, U11.2, U12.2
R7: R27.2, R28.1, SV13.6, U13.2, U14.2
R8: R31.2, R32.1, SV15.6, U15.2, U16.2
R9: R35.2, R36.1, SV17.6, U17.2, U18.2

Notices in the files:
parts and their libraries:
SparkFun-Capacitors: Licensing: Creative Commons ShareAlike 4.0 International - https://creativecommons.org/licenses/by-sa/4.0
